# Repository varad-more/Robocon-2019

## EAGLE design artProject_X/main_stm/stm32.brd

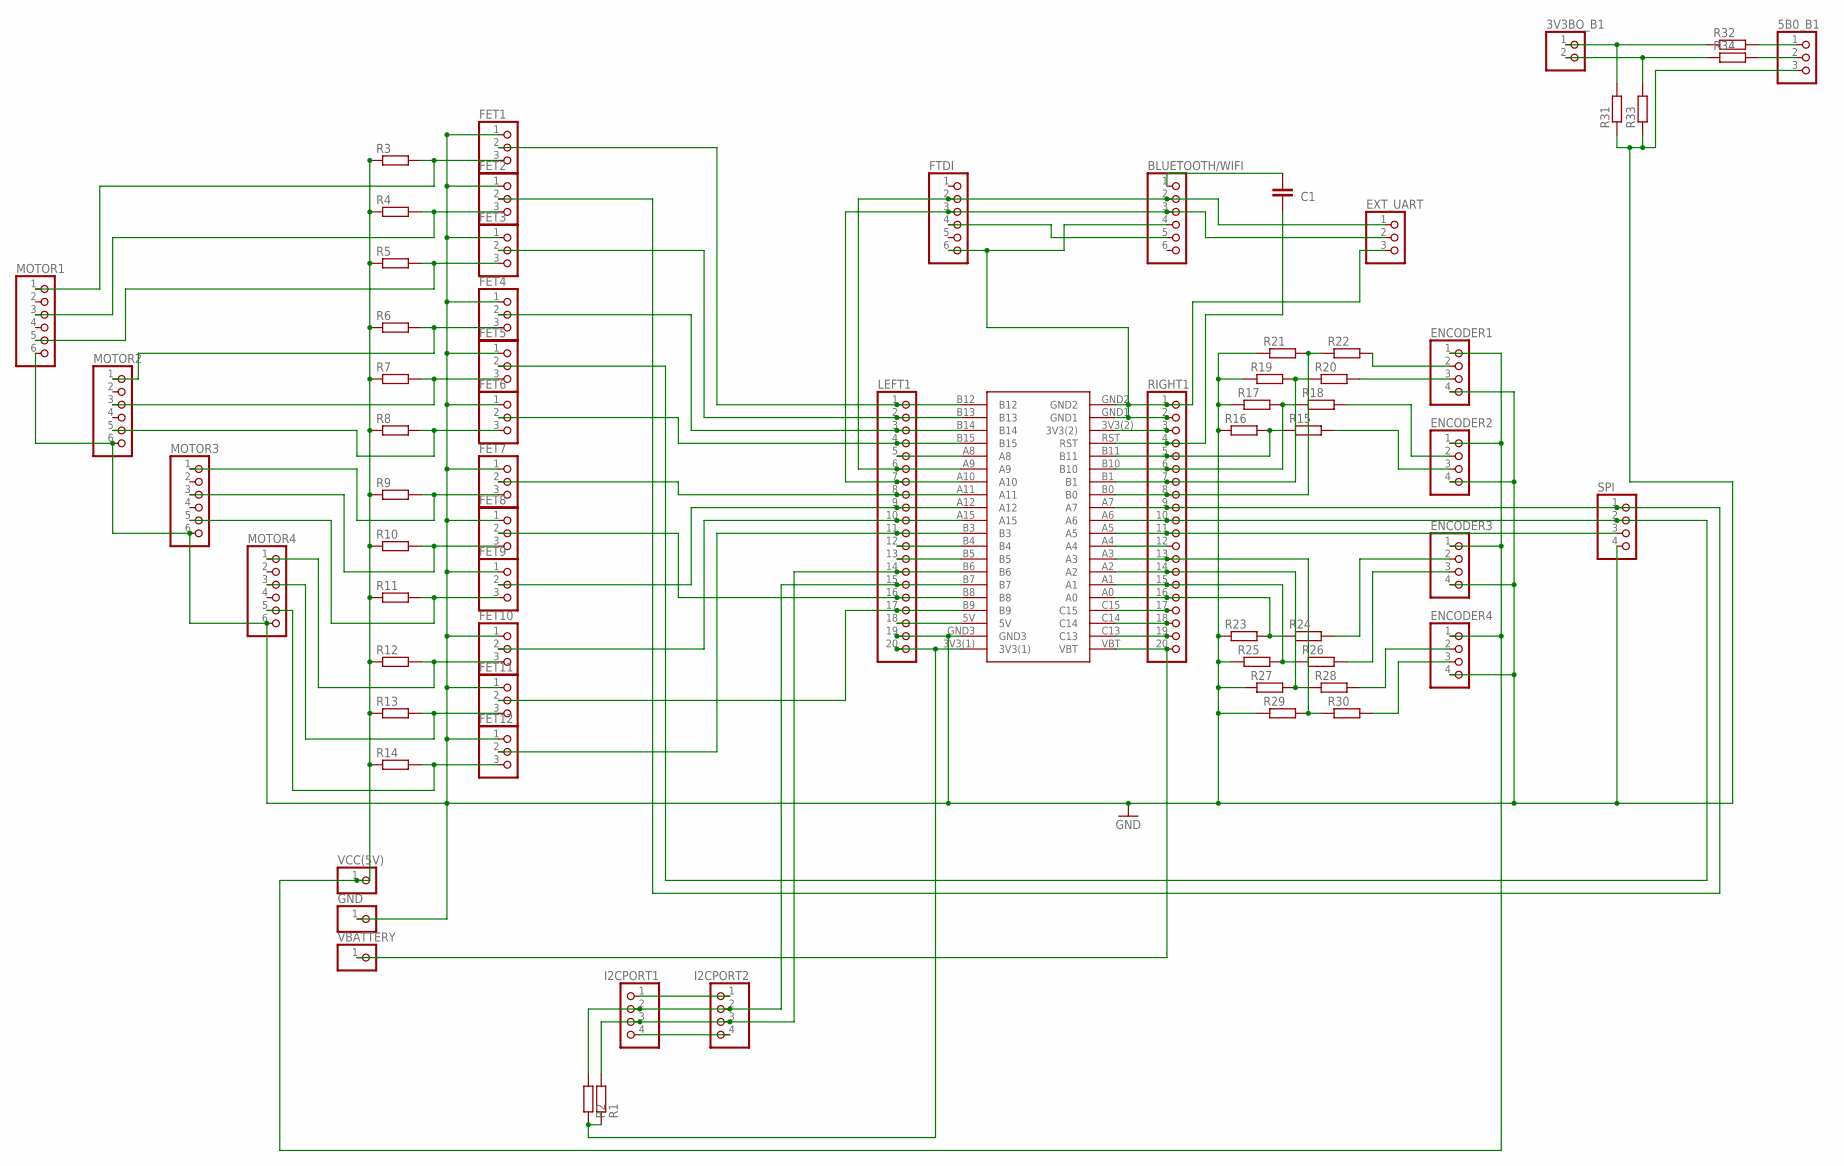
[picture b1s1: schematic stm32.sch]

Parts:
3V3BO_B1: PINHD-1X2; 1X02
5B0_B1: PINHD-1X3; 1X03
BLUETOOTH/WIFI: PINHD-1X6; 1X06
C1: C-EU025-030X050; C025-030X050
ENCODER1, ENCODER2, ENCODER3, ENCODER4: PINHD-1X4; 1X04
EXT_UART: PINHD-1X3; 1X03
FET1, FET2, FET3, FET4, FET5, FET6, FET7, FET8, FET9, FET10, FET11, FET12: PINHD-1X3; 1X03
FTDI: PINHD-1X6; 1X06
GND: PINHD-1X1; 1X01
I2CPORT1, I2CPORT2: PINHD-1X4; 1X04
LEFT1: PINHD-1X20; 1X20
MOTOR1, MOTOR2, MOTOR3, MOTOR4: PINHD-1X6; 1X06
R1, R2, R3, R4, R5, R6, R7, R8, R9, R10, R11, R12, R13, R14, R15, R16, R17, R18, R19, R20, R21, R22, R23, R24, R25, R26, R27, R28, R29, R30, R31, R32, R33, R34: R-EU_0204/5; 0204/5
RIGHT1: PINHD-1X20; 1X20
SPI: PINHD-1X4; 1X04
U$1: STM32THROUGH_HOLE; STM32
VBATTERY: PINHD-1X1; 1X01
VCC(5V): PINHD-1X1; 1X01

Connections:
5V: ENCODER1.1, ENCODER2.1, ENCODER3.1, ENCODER4.1, R3.1, R4.1, R5.1, R6.1, R7.1, R8.1, R9.1, R10.1, R11.1, R12.1, R13.1, R14.1, VCC(5V).1
B0: ENCODER1.2, R22.2
B1: ENCODER1.3, R20.2
GND: 5B0_B1.3, ENCODER1.4, ENCODER2.4, ENCODER3.4, ENCODER4.4, FET1.1, FET2.1, FET3.1, FET4.1, FET5.1, FET6.1, FET7.1, FET8.1, FET9.1, FET10.1, FET11.1, FET12.1, GND.1, LEFT1.19, MOTOR1.6, MOTOR2.6, MOTOR3.6, MOTOR4.6, R16.1, R17.1, R19.1, R21.1, R23.1, R25.1, R27.1, R29.1, R31.1, R33.1, SPI.4, U$1.GND3
unnamed: 3V3BO_B1.1, R31.2, R32.1
unnamed: FET3.2, LEFT1.2, U$1.B13
unnamed: LEFT1.20, R1.1, R2.1, U$1.3V3(1)
unnamed: FET4.2, LEFT1.3, U$1.B14
unnamed: FET6.2, LEFT1.4, U$1.B15
unnamed: LEFT1.5, U$1.A8
unnamed: BLUETOOTH/WIFI.2, EXT_UART.1, FTDI.2, LEFT1.6, U$1.A9
unnamed: LEFT1.18, U$1.5V
unnamed: BLUETOOTH/WIFI.3, EXT_UART.2, FTDI.3, LEFT1.7, U$1.A10
unnamed: BLUETOOTH/WIFI.5, FTDI.4
unnamed: FET10.2, LEFT1.10, U$1.A15
unnamed: FET7.2, LEFT1.8, U$1.A11
unnamed: FET9.2, LEFT1.9, U$1.A12
unnamed: BLUETOOTH/WIFI.1, C1.2
unnamed: FET12.2, LEFT1.11, U$1.B3
unnamed: I2CPORT1.2, I2CPORT2.2, LEFT1.15, R2.2, U$1.B7
unnamed: FET8.2, LEFT1.16, U$1.B8
unnamed: FET11.2, LEFT1.17, U$1.B9
unnamed: LEFT1.12, U$1.B4
unnamed: BLUETOOTH/WIFI.4, EXT_UART.3, FTDI.6, RIGHT1.1, RIGHT1.2, U$1.GND1, U$1.GND2
unnamed: 3V3BO_B1.2, R33.2, R34.1
unnamed: RIGHT1.20, U$1.VBT, VBATTERY.1
unnamed: RIGHT1.19, U$1.C13
unnamed: RIGHT1.18, U$1.C14
unnamed: RIGHT1.17, U$1.C15
unnamed: R23.2, R24.1, RIGHT1.16, U$1.A0
unnamed: I2CPORT1.1, I2CPORT2.1
unnamed: R25.2, R26.1, RIGHT1.15, U$1.A1
unnamed: R27.2, R28.1, RIGHT1.14, U$1.A2
unnamed: I2CPORT1.3, I2CPORT2.3, LEFT1.14, R1.2, U$1.B6
unnamed: R29.2, R30.1, RIGHT1.13, U$1.A3
unnamed: RIGHT1.12, U$1.A4
unnamed: RIGHT1.11, SPI.3, U$1.A5
unnamed: 5B0_B1.1, R32.2
unnamed: FET5.2, RIGHT1.10, SPI.2, U$1.A6
unnamed: 5B0_B1.2, R34.2
unnamed: R21.2, R22.1, RIGHT1.8, U$1.B0
unnamed: R17.2, R18.1, RIGHT1.6, U$1.B10
unnamed: I2CPORT1.4, I2CPORT2.4
unnamed: RIGHT1.3, U$1.3V3(2)
unnamed: C1.1, RIGHT1.4, U$1.RST
unnamed: R15.1, R16.2, RIGHT1.5, U$1.B11
unnamed: FET1.2, LEFT1.1, U$1.B12
unnamed: LEFT1.13, U$1.B5
unnamed: FET1.3, MOTOR1.1, R3.2
unnamed: FET2.3, MOTOR1.3, R4.2
unnamed: FET3.3, MOTOR1.5, R5.2
unnamed: FET4.3, MOTOR2.1, R6.2
unnamed: FET5.3, MOTOR2.3, R7.2
unnamed: FET6.3, MOTOR2.5, R8.2
unnamed: FET7.3, MOTOR3.1, R9.2
unnamed: FET8.3, MOTOR3.3, R10.2
unnamed: FET9.3, MOTOR3.5, R11.2
unnamed: FET11.3, MOTOR4.3, R13.2
unnamed: FET10.3, MOTOR4.1, R12.2
unnamed: FET12.3, MOTOR4.5, R14.2
unnamed: FET2.2, RIGHT1.9, SPI.1, U$1.A7
unnamed: R19.2, R20.1, RIGHT1.7, U$1.B1
unnamed: ENCODER3.2, R24.2
unnamed: ENCODER3.3, R26.2
unnamed: ENCODER4.2, R28.2
unnamed: ENCODER4.3, R30.2
unnamed: ENCODER2.2, R18.2
unnamed: ENCODER2.3, R15.2

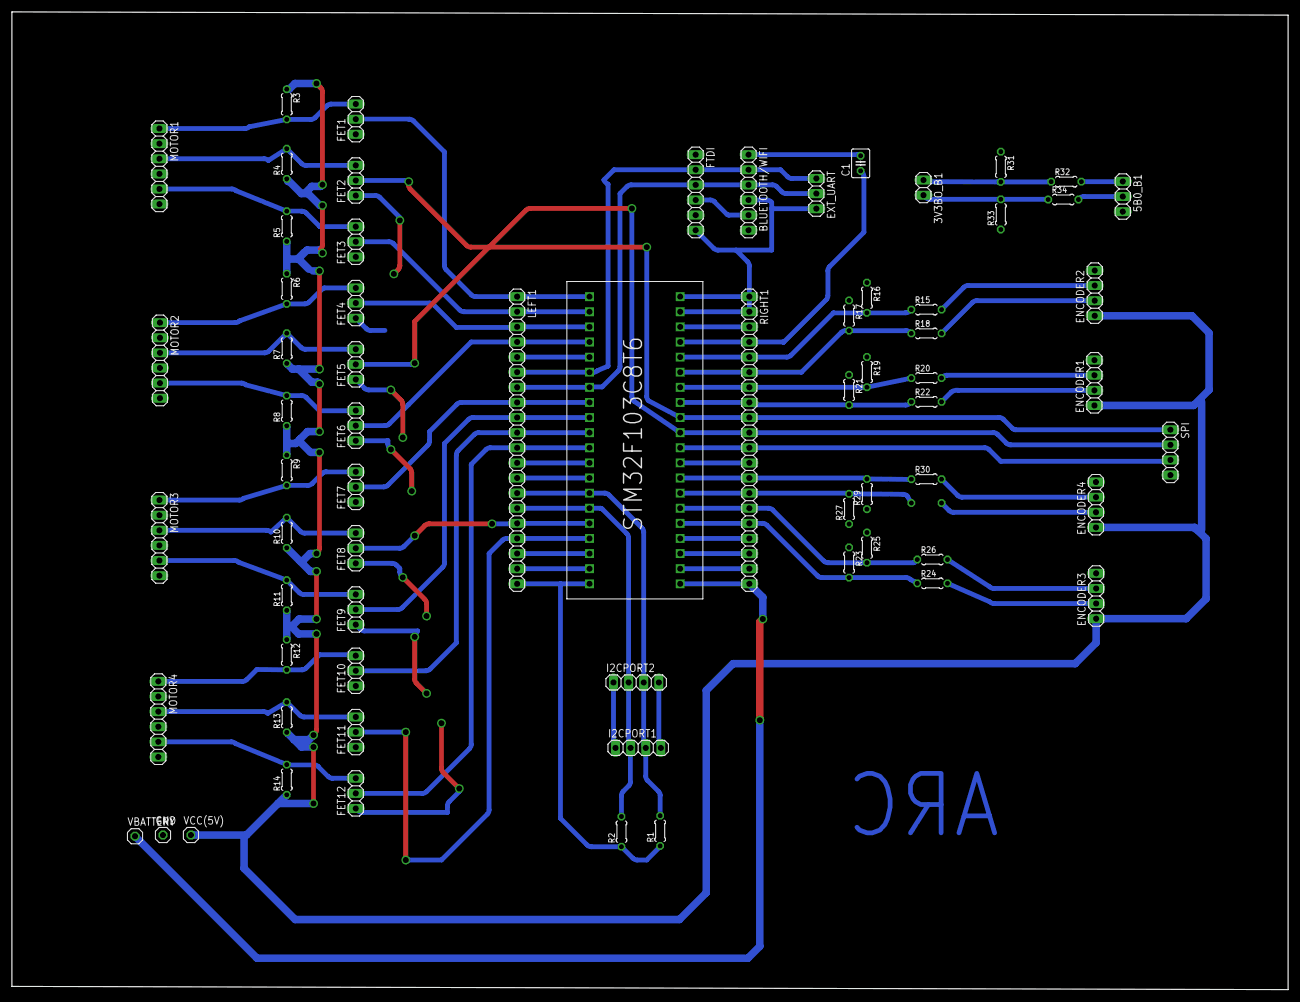
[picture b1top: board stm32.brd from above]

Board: 2 copper layers, 214.5 x 164.3 mm, 69 parts (1 on the bottom side), 68 nets.
